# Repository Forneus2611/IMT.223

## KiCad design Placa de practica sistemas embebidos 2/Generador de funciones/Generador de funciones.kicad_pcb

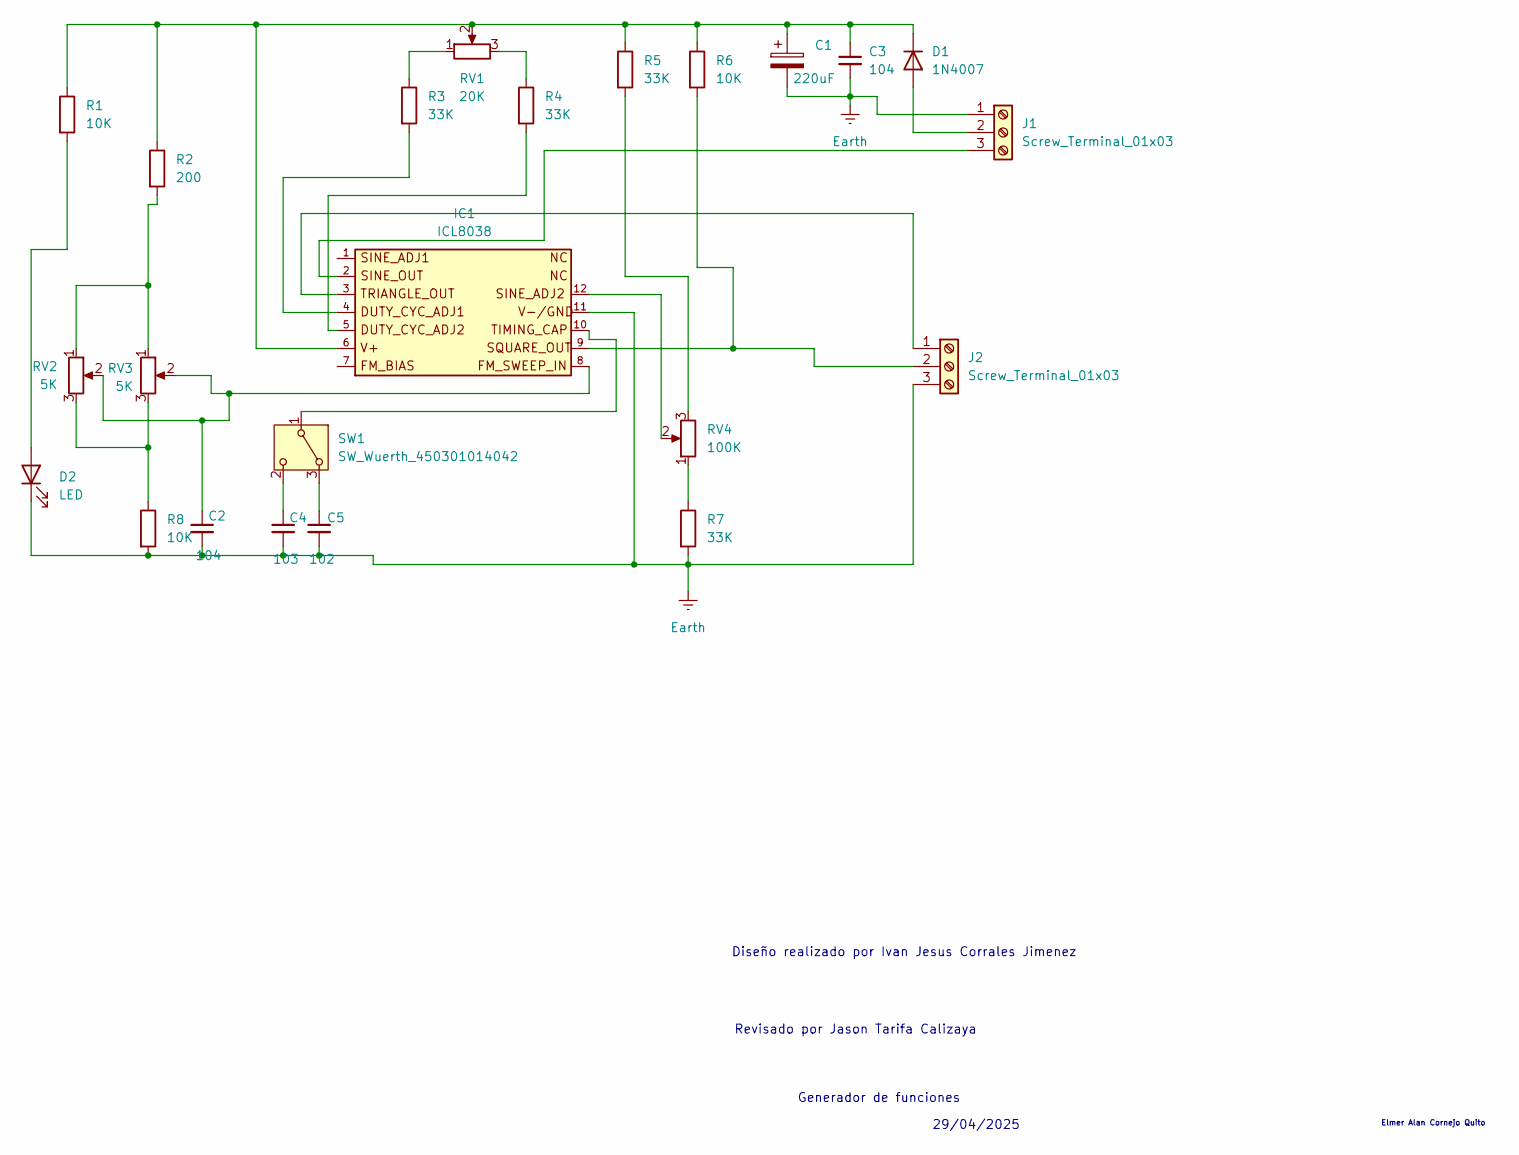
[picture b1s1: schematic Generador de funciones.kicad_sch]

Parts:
C1: 220uF; CP_Radial_D10.0mm_P3.50mm
C2: 104; C_Disc_D5.0mm_W2.5mm_P2.50mm
C3: 104; C_Disc_D6.0mm_W2.5mm_P5.00mm
C4: 103; C_Disc_D7.0mm_W2.5mm_P5.00mm
C5: 102; C_Disc_D7.0mm_W2.5mm_P5.00mm
D1: 1N4007; D_DO-41_SOD81_P10.16mm_Horizontal
D2: LED; LED_D3.0mm
IC1: ICL8038
J1, J2: Screw_Terminal_01x03; TerminalBlock_Phoenix_MKDS-3-3-5.08_1x03_P5.08mm_Horizontal
R1, R6, R8: 10K; R_Axial_DIN0207_L6.3mm_D2.5mm_P7.62mm_Horizontal
R2: 200; R_Axial_DIN0207_L6.3mm_D2.5mm_P7.62mm_Horizontal
R3, R4, R5, R7: 33K; R_Axial_DIN0207_L6.3mm_D2.5mm_P7.62mm_Horizontal
RV1: 20K; Potentiometer_Bourns_3339P_Vertical_HandSoldering
RV2: 5K; Potentiometer_Bourns_3386W_Horizontal
RV3: 5K; Potentiometer_Bourns_3339P_Vertical_HandSoldering
RV4: 100K; Potentiometer_Bourns_3339P_Vertical_HandSoldering
SW1: SW_Wuerth_450301014042; SW_Slide-03_Wuerth-WS-SLTV_10x2.5x6.4_P2.54mm

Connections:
Earth: C1.2, C2.2, C3.2, C4.2, C5.2, D2.1 (K), IC1.11, J1.1, J2.3, R7.2, R8.2
unnamed: C2.1, IC1.8, RV2.2, RV3.2
unnamed: D1.2 (A), J1.2
unnamed: C1.1, C3.1, D1.1 (K), IC1.6, R1.1, R2.1, R5.1, R6.1, RV1.2
unnamed: D2.2 (A), R1.2
unnamed: IC1.4, R3.2
unnamed: IC1.5, R4.2
unnamed: IC1.12, RV4.2
unnamed: IC1.2, J1.3
unnamed: IC1.3, J2.1
unnamed: IC1.9, J2.2, R6.2
unnamed: R2.2, RV2.1, RV3.1
unnamed: R3.1, RV1.1
unnamed: R4.1, RV1.3
unnamed: R5.2, RV4.3
unnamed: R7.1, RV4.1
unnamed: R8.1, RV2.3, RV3.3
unnamed: C5.1, SW1.3 (A)
unnamed: IC1.10, SW1.1 (B)
unnamed: C4.1, SW1.2 (C)

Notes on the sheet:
Revisado por Jason Tarifa Calizaya
Diseño realizado por Ivan Jesus Corrales Jimenez
Elmer Alan Cornejo Quito
29/04/2025
Generador de funciones

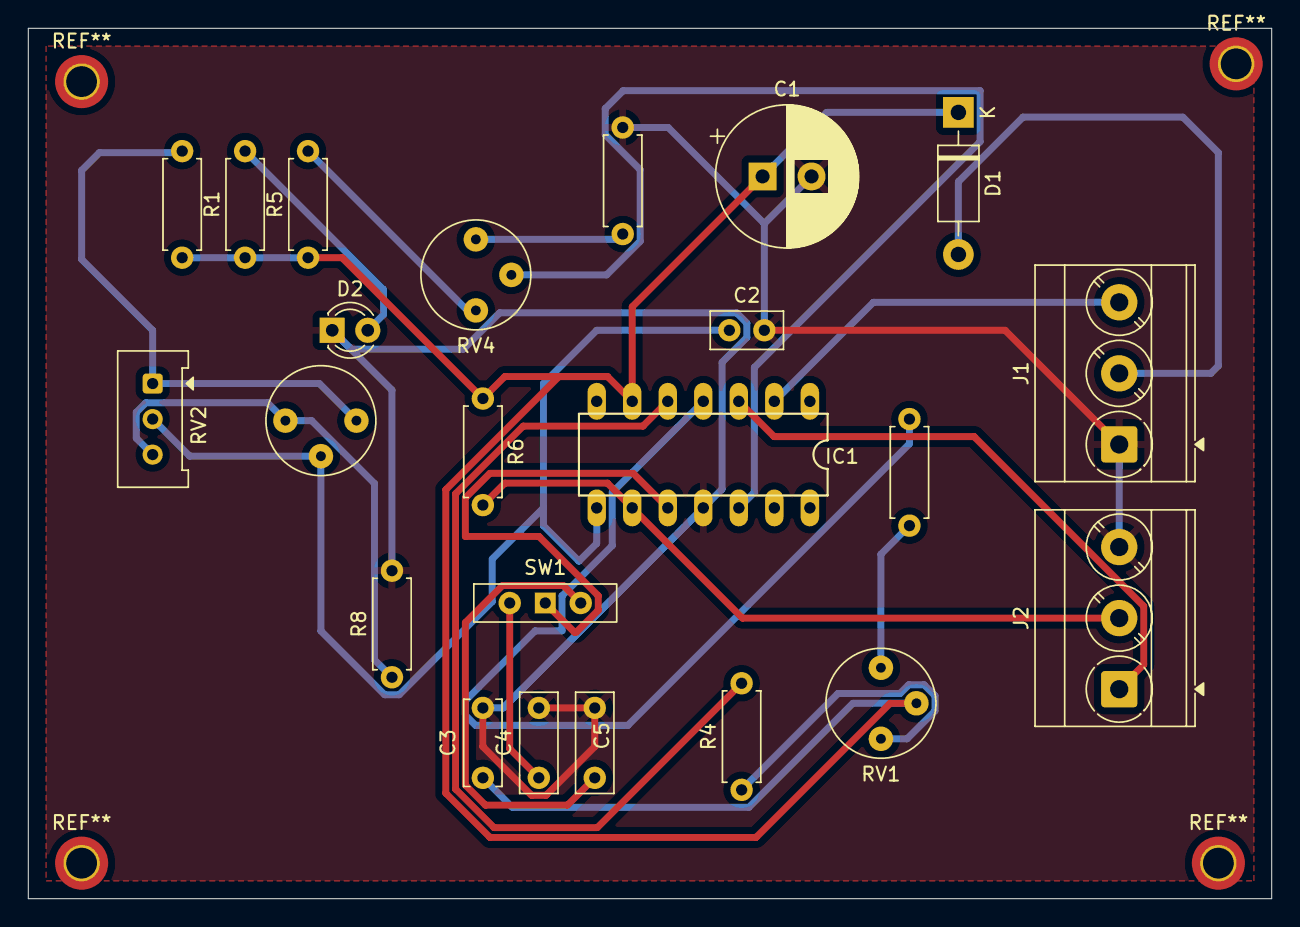
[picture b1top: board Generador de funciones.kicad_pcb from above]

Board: 2 copper layers, 88.9 x 62.2 mm, 23 parts (0 on the bottom side), 20 nets.

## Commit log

2025-02-13 Inicio
2025-02-13 Se añadio una nueva practica de prender leds
2025-02-18 Practicas con placas F767ZII, F429ZI, L432KC
2025-03-18 Se añadio ejercicios de practica con el stm32smartcube
2025-03-18 nueva practica
2025-03-25 adiccion de examenes de primer elemento de competencia
2025-04-29 Se anadio la practica de la PCB
2025-04-29 Se anadio los archvios gerber
